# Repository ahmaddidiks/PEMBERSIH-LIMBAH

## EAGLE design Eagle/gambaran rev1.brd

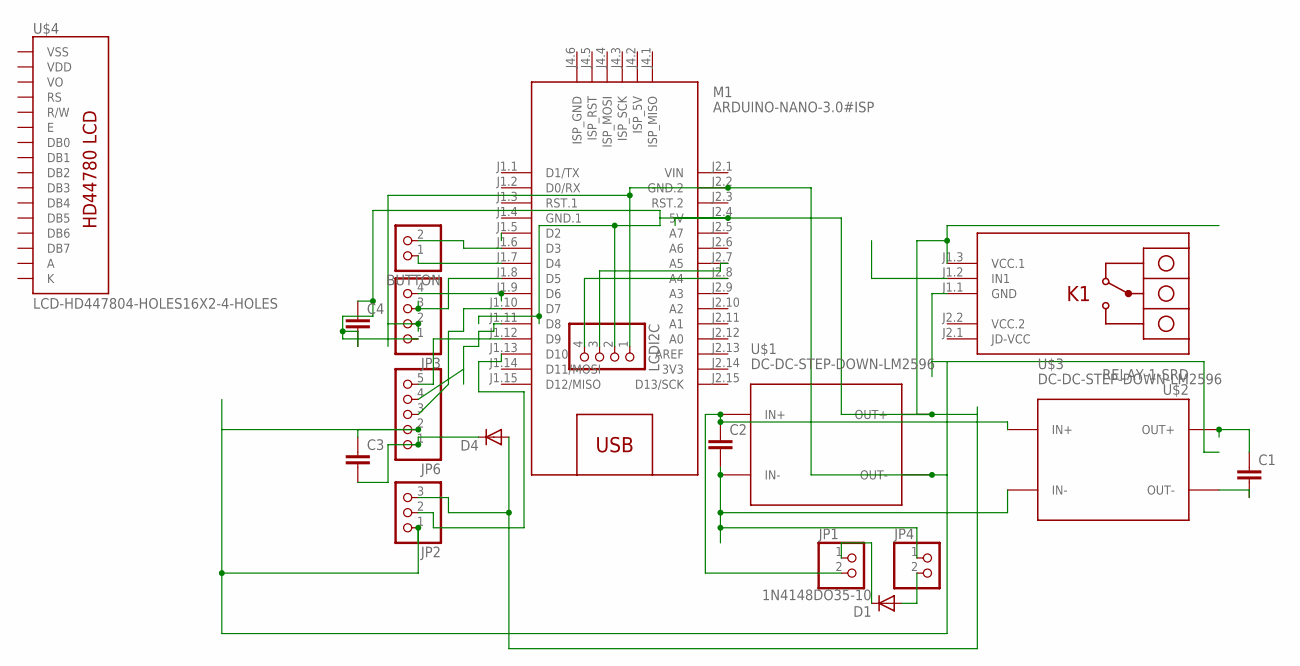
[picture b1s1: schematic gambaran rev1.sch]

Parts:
BUTTON: PINHD-1X2/90; 1X02/90
C1, C2, C3, C4: C2.5/6; C2.5-6
D1, D4: 1N4148DO35-10; DO35-10
JP1, JP4: PINHD-1X2/90; 1X02/90
JP2: PINHD-1X3; 1X03
JP3: PINHD-1X4/90; 1X04/90
JP6: PINHD-1X5; 1X05
LCDI2C: PINHD-1X4/90; 1X04/90
M1: ARDUINO-NANO-3.0#ISP
U$1, U$3: DC-DC-STEP-DOWN-LM2596
U$2: RELAY-1-SRD
U$4: LCD-HD447804-HOLES16X2-4-HOLES; LCD-16X2-4HOLES

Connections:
3V3: M1.J2.14 (3V3)
A: U$4.15 (A)
GND.1: M1.J1.4 (GND.1)
K: U$4.16 (K)
unnamed: C2.2, JP4.1, U$1.IN-, U$3.IN-
unnamed: C2.1, JP1.2, U$1.IN+, U$3.IN+
unnamed: C3.2, D4.C, JP6.1
unnamed: C4.1, C4.2, D4.A, JP2.3, JP3.1, LCDI2C.2, M1.J2.4 (5V), U$1.OUT+, U$2.J1.3 (VCC.1)
unnamed: LCDI2C.3, M1.J2.7 (A5)
unnamed: LCDI2C.4, M1.J2.8 (A4)
unnamed: C1.1, U$3.OUT+
unnamed: C3.1, JP2.1, JP3.2, JP6.2, LCDI2C.1, M1.J2.2 (GND.2), U$1.OUT-, U$2.J1.1 (GND)
unnamed: D1.C, JP1.1
unnamed: D1.A, JP4.2
unnamed: C1.2, U$3.OUT-
unnamed: BUTTON.2, M1.J1.6 (D3)
unnamed: BUTTON.1, M1.J1.7 (D4)
unnamed: JP3.4, M1.J1.9 (D6)
unnamed: JP6.3, M1.J1.10 (D7)
unnamed: JP6.4, M1.J1.11 (D8)
unnamed: JP3.3, M1.J1.8 (D5)
unnamed: JP6.5, M1.J1.12 (D9)
unnamed: JP2.2, M1.J1.13 (D10)
VCC.2: U$2.J2.2 (VCC.2)
VDD: U$4.2 (VDD)
VIN: M1.J2.1 (VIN)
VSS: U$4.1 (VSS)

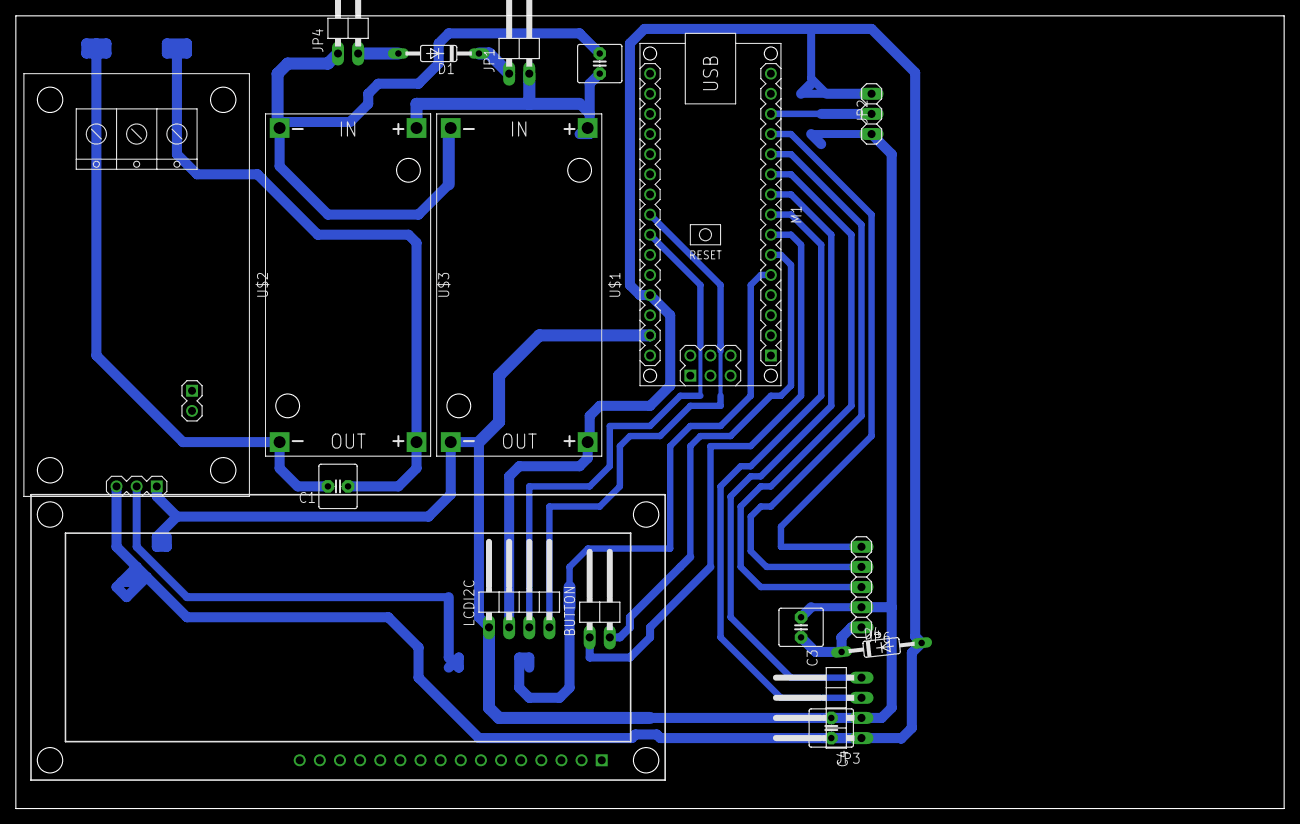
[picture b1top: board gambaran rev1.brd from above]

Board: 2 copper layers, 160.0 x 100.0 mm, 18 parts (0 on the bottom side), 19 nets.

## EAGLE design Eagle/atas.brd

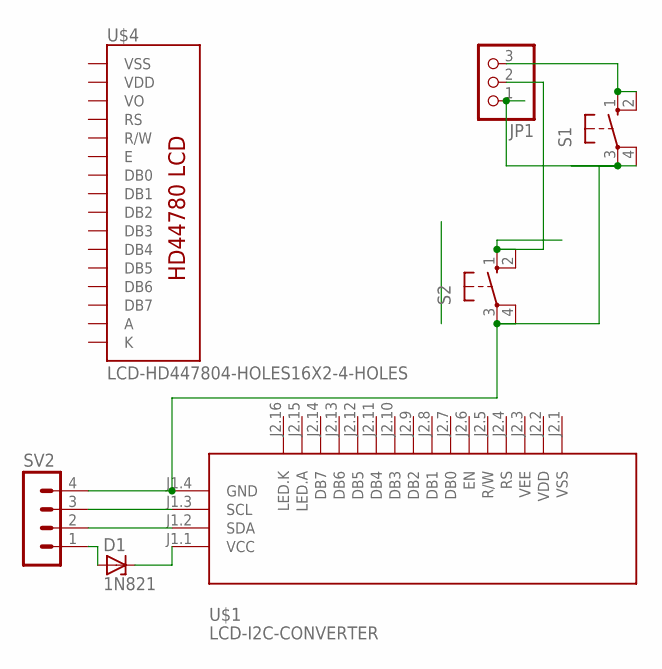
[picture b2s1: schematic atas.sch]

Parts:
D1: 1N821; DO35Z10
JP1: PINHD-1X3/90; 1X03/90
S1, S2: 10-XX; B3F-10XX
SV2: MA04-1
U$1: LCD-I2C-CONVERTER
U$4: LCD-HD447804-HOLES16X2-4-HOLES; LCD-16X2-4HOLES

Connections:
A: U$4.15 (A)
K: U$4.16 (K)
unnamed: JP1.3, S1.1 (S), S1.2 (S1)
unnamed: JP1.2, S2.1 (S), S2.2 (S1)
unnamed: JP1.1, S1.3, S1.4 (P1), S2.3, S2.4 (P1), SV2.4, U$1.J1.4 (GND)
unnamed: D1.A, SV2.1
unnamed: SV2.3, U$1.J1.3 (SCL)
unnamed: SV2.2, U$1.J1.2 (SDA)
unnamed: D1.C, U$1.J1.1 (VCC)
VDD: U$4.2 (VDD)
VSS: U$4.1 (VSS)

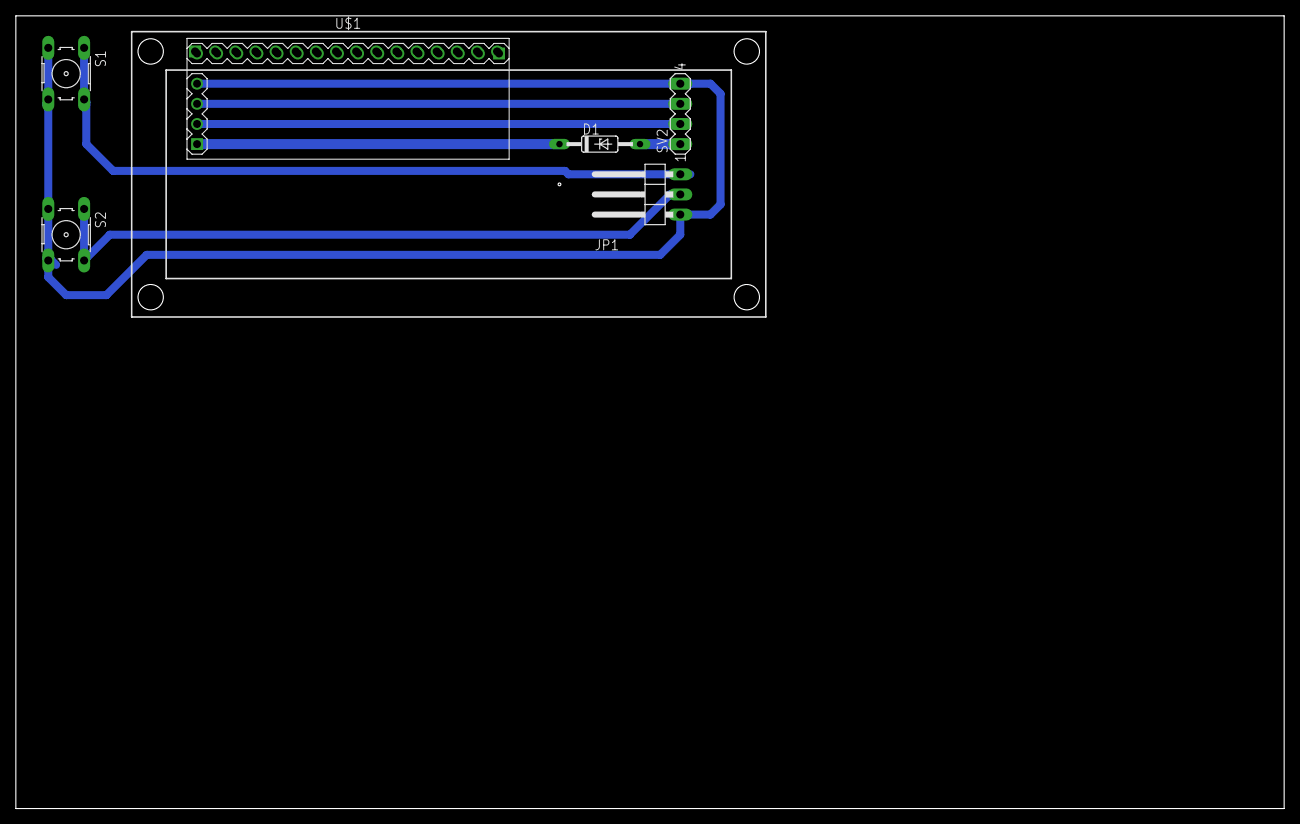
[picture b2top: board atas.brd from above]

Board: 2 copper layers, 160.0 x 100.0 mm, 7 parts (0 on the bottom side), 7 nets.

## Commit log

2020-10-24 code
2020-10-24 codingan awal

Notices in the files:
parts and their libraries:
diy-modules+i2c: Released under the Creative Commons Attribution 4.0 International License: http://creativecommons.org/licenses/by/4.0
